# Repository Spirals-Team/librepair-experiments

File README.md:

# repairnator-experiments

This is an open-science repository with data related to ["How to Design a Program Repair Bot? Insights from the Repairnator Project"](https://hal.inria.fr/hal-01691496/document) (ICSE 2018) and [Repairnator patches programs automatically](https://ubiquity.acm.org/article.cfm?id=3349589), (Ubiquity, Association for Computing Machinery, 2019).

```Bibtex
@inproceedings{repairnator,
 title = {How to Design a Program Repair Bot? Insights from the Repairnator Project},
 author = {Urli, Simon and Yu, Zhongxing and Seinturier, Lionel and Monperrus, Martin},
 booktitle = {Proceedings of the 40th International Conference on Software Engineering},
 year = {2018}
}
```

This repository aims to contain the code of the failing Java projects and also information about the bugs reproduction, test failures and repair attempts using three different repair tools: [NPEFix](https://github.com/SpoonLabs/npefix), [Nopol](https://github.com/SpoonLabs/nopol), and [Astor](https://github.com/SpoonLabs/astor).

## Content of the repository

The structure of the repository is as follows:
* Branch `master` contains the `builds` folder and the documentation of this repository;
* The `builds` folder contains a specific JSON file obtained using the Travis CI API for every Travis CI build failure related to Java programs that use Maven as building tool;
* The `jobs` folder contains a subfolder for every build and each of them contains as many JSON files (obtained using the Travis CI API) as the number of jobs associated with that build;
* For each of these failing builds, there is a specific branch with all the information related to the building of the project, bug reproduction, failing tests and repair attempts.

More details about every entry listed above will be provided in the subsequent sections.

## Statistics

The repository contains the builds collected in the period February 2017 - September 2018.

There are currently 14.132 build JSON files in the `builds` folder, each of them associated with a Continuous Integration (CI) build failure of a Java program that uses Maven as building tool.

The name of these JSON files corresponds to the Travis CI build identifier and their content is the result of the Travis CI API V3 ```GET /build/{build.id}```. More details can be found on the [official documentation](https://docs.travis-ci.com/user/developer/#api-v3).

The `jobs` folder has a specific subfolder for every build (except for 25 builds in which the data are no more available through the Travis CI API) and the name of these subfolders corresponds with the build id to which they are associated. Every subfolder related to a build contains a distinct JSON file for every job associated with that build. The name of these JSON files corresponds to the Travis CI job identifier and their content is the result of the Travis CI API V3 ```GET /job/{job.id}```.

There are 14.132 different branches (excluding master branch), each of them associated with a build failure. In particular, every branch can have 2, 3 or 4 commits, as reported in the following table:

|                            | 2 commits   | 3 commits   | 4 commits   |
|----------------------------|:-----------:|:-----------:|:-----------:|
| **Number of the branches** | 15          | 13.870      | 247         |

Most of the branches have 3 commits, where:
* The first one is the failing one;
* The second one contains metadata and log infomation regarding the building of the project;
* The third one adds other information about the failure and the reproduction of the bug. In addition, it can contain a patch developed by an automatic program repair technique, if any.

The branches that have 2 commits have the same information of the branches with 3 commits, and the only difference is that it has been created a single commit with all the data that usually are separated in the second and the third commit.

The branches that have 4 commits have one commit (the third one) that contains also the human patch.

## Builds information extracted using Travis CI API

### States of the collected failing builds

A build can have different states, and as reported in the [official documentation of Travis CI](https://docs.travis-ci.com/user/for-beginners/#breaking-the-build), a build is considered broken when one or more of its jobs complete with a state that is not passed: `errored`, `failed`, or `canceled`.

In the following table, it is reported the number of collected builds based on their state:

|                            | failed      | passed      | errored     | canceled  |
|----------------------------|:-----------:|:-----------:|:-----------:|:---------:|
| **Number of builds**       | 13.178      | 895         | 47          | 12        |

### Trigger events of the collected failing builds

Every build is triggered by an event. In particular, in the following table we see the number of the collected builds that have been triggered by a specific event:

|                            | push        | pull request  | cron        | api      |
|----------------------------|:-----------:|:-------------:|:-----------:|:--------:|
| **Number of builds**       | 7.169       | 6.264         | 539         | 160      |

The event type `cron` means that the build has been triggered via the [Travis CI cron jobs](https://docs.travis-ci.com/user/cron-jobs/), that can run builds at regular scheduled intervals independently of whether any commits were pushed to the repository.

The event type `api` means that the build has been triggered using the Travis CI API.

### Duration of the collected failing builds

Using the information extracted from the Travis CI API, it is possible to know the duration of a build, where the term `duration` is intended as the wall clock time in seconds to produce and execute a build.

The following table shows the number of the builds per different intervals of duration:

|                                            | Number of the builds   |
|:------------------------------------------:|-----------------------:|
| **0 &lt; duration &le; 100**               |                 1.527  |
| **100 &lt; duration &le; 500**             |                 3.948  |
| **500 &lt; duration &le; 1.000**           |                 1.443  |
| **1.000 &lt; duration &le; 5.000**         |                 3.397  |
| **5.000 &lt; duration &le; 10.000**        |                 1.220  |
| **10.000 &lt; duration &le; 25.000**       |                 2.172  |
| **25.000 &lt; duration &le; 50.000**       |                   408  |
| **duration &gt; 50.000**                   |                    17  |

The minimum duration recorded has been 3 seconds (`build` [357685462](https://github.com/repairnator/repairnator-experiments/blob/master/builds/357685462.json), `branch` [as0kir-topjava-357685462-20180324-053259](https://github.com/repairnator/repairnator-experiments/tree/as0kir-topjava-357685462-20180324-053259)), while the maximum duration recorded has been 60.035 seconds (`build` [247511890](https://github.com/repairnator/repairnator-experiments/blob/master/builds/247511890.json), `branch` [apache-flink-247511890-20170627-234202_bugonly](https://github.com/repairnator/repairnator-experiments/tree/apache-flink-247511890-20170627-234202_bugonly)).

## Jobs information extracted using Travis CI API

### States of the jobs associated with a build

Using the Travis CI API, it is possibile to know also the state of the jobs associated with a specific build. In particular, a job can have four different states: `passed`, `errored`, `failed`, and `canceled`. As reported in the [official documentation of Travic CI](https://docs.travis-ci.com/user/for-beginners/#breaking-the-build), when one or more jobs have a state different from `passed`, the associated build is considered broken.

In the following table, it is reported the number of jobs associated with the collected builds based on their state:

|                            | passed      | errored     | failed      | canceled  |
|----------------------------|:-----------:|:-----------:|:-----------:|:---------:|
| **Number of jobs**         | 37.738      | 144         | 23.962      | 2.945     |

### Number of errored jobs per build

When a job is classified as `errored`, it means that a command in the `before_install`, `install`, or `before_script` phase returned a non-zero exit code. The job stops immediately.

In the following table it is possibile to see the number of errored jobs per build:

| Number of the errored jobs | Number of the builds |
|----------------------------|---------------------:|
| 0                          |               14.003 |
| 1                          |                   87 |
| 2                          |                    8 |
| 3                          |                    3 |
| 4                          |                    5 |
| 5                          |                    0 |
| 6                          |                    0 |
| > 6                        |                    1 |

The highest number of the errored jobs per build is 12 (`build` [332193968](https://github.com/repairnator/repairnator-experiments/blob/master/builds/332193968.json), `branch` [GJL-flink-332193968-20180123-111656_bugonly](https://github.com/repairnator/repairnator-experiments/tree/GJL-flink-332193968-20180123-111656_bugonly)). 

### Number of failed jobs per build

When a job is classified as `failed`, it means that a command in the `script` phase returned a non-zero exit code. The job continues to run until it completes.

In the following table it is possibile to see the number of failed jobs per build:

| Number of the failed jobs | Number of the builds |
|---------------------------|---------------------:|
| 0                         |                  926 |
| 1                         |                8.554 |
| 2                         |                2.514 |
| 3                         |                  901 |
| 4                         |                  512 |
| 5                         |                  187 |
| 6                         |                  193 |
| > 6                       |                  320 |

The highest number of the failed jobs per build is 58 (`build` [421480538](https://github.com/repairnator/repairnator-experiments/blob/master/builds/421480538.json) - `branch` [JWGmeligMeyling-blaze-persistence-421480538-20180828-125625](https://github.com/repairnator/repairnator-experiments/tree/JWGmeligMeyling-blaze-persistence-421480538-20180828-125625), and `build` [421505900](https://github.com/repairnator/repairnator-experiments/blob/master/builds/421505900.json) - `branch` [JWGmeligMeyling-blaze-persistence-421505900-20180828-141855](https://github.com/repairnator/repairnator-experiments/tree/JWGmeligMeyling-blaze-persistence-421505900-20180828-141855)).

### Number of canceled jobs per build

When a job is classified as `canceled`, it means that a user cancels the job before it completes.

In the following table it is possibile to see the number of canceled jobs per build:

| Number of the canceled jobs | Number of the builds |
|-----------------------------|---------------------:|
| 0                           |               13.834 |
| 1                           |                  159 |
| 2                           |                   15 |
| 3                           |                    4 |
| 4                           |                    4 |
| 5                           |                    0 |
| 6                           |                    2 |
| > 6                         |                   89 |

The highest number of the canceled jobs per build is 36. The are 41 builds with 36 canceled jobs (e.g., the `build` [335090924](https://github.com/repairnator/repairnator-experiments/blob/master/builds/335090924.json), `branch` [matsim-org-matsim-335090924-20180130-113656_bugonly](https://github.com/repairnator/repairnator-experiments/tree/matsim-org-matsim-335090924-20180130-113656_bugonly)).

## Builds information extracted using Repairnator

The data about bugs reproduction, test failures and repair attempts is stored in a specific branch for every build failure. In particular, every branch is linked to a build JSON file in `master` branch and, as well as containing the source code of the buggy program, it also has some files with the keyword `repairnator`in their name. 

### repairnator.json files

Every branch has a file called `repairnator.json` that contains the data reported in the following table:

| Parameter                | Description                                                                               |
|:-------------------------|:------------------------------------------------------------------------------------------|
| bugType                  | The type of the failing build.                                                             |
| bugCommit                | The URL of the bug commit in which it is possible to see the diff with the previous one.  |
| error-types              | The types of errors that occurred during the building of the project.                      |
| failingModule            | The failing Maven module.                                    |
| failing-test-cases       | The list of the failing test cases.                                                       |
| hostname                 | The hostname used to run the Repairnator inspector.                                          |
| metrics                  | It contains information about the program associated with the failing build, such as the number of program files, the number of test cases and the number of used libraries. It also contains other information, such as the duration expressed in seconds to reproduce the bug, the date of the buggy build, and the date of the bug reproduction.                                                                                                      |
| repo                     | The name of the repository associated with the failing build.                             |
| totalNumberErroringTests | The total number of the erroring test cases.                                              |
| totalNumberFailingTests  | The total number of the failing test cases.                                               |
| totalNumberRunningTests  | The total number of the running test cases.                                               |
| totalNumberSkippingTests | The total number of the skipping test cases.                                              |

### Repairnator Maven files

Repairnator also collects information about the different phases of the Maven build life cycle. In particual, there are four different files. It is possible to see the number of the branches that have these files in the following table:

| File                                      | Number of the branches |
|:------------------------------------------|-----------------------:|
| repairnator.maven.buildproject.log        |                 12.855 |
| repairnator.maven.testproject.log         |                 12.855 |
| repairnator.maven.computeclasspath.log    |                 12.799 |
| repairnator.maven.resolvedependency.log   |                  7.841 |

* **repairnator.maven.buildproject.log**: it contains log information about the building of a project, such as the operations related to the goals of Apache Maven Resources plugin;
* **repairnator.maven.testproject.log**: it contains information about the execution of the test suite, such as the name of the executed test cases, and the number of the failing, running or skipped tests;
* **repairnator.maven.computeclasspath.log**: it contains log information about the creation of the classpath file;
* **repairnator.maven.resolvedependency.log**: it contains log information about the download of the necessary dependecies in order to build the project.

### Repairnator Nopol files

Nopol is one of the three program repair tools used in order to try to generate a patch for the failing builds. Nopol has been used since February 2017. The file `repairnator.nopol.results` contains information about its execution, such as its configuration and the allocated time. In the following table it is possible to see the number of the branches that contain this file:

| File                                      | Number of the branches |
|:------------------------------------------|-----------------------:|
| repairnator.nopol.results                 |                  8.910 |

### Repairnator NPEFix files

NPEFix is the second program repair tool used during the experiment and it has been used since August 2017. In particular, it has been exploited only when a `NullPointerException` has been encountered during the execution of the test suite. In the following table, there are the different files associated with the execution of NPEFix and the number of branches that have these files:

| File                                      | Number of the branches |
|:------------------------------------------|-----------------------:|
| repairnator.maven.nperepair.log           |                    921 |
| repairnator.maven.npefix.log              |                    715 |
| repairnator.npefix.results                |                    289 |

* **repairnator.maven.nperepair.log**: it contains Maven log information about the building of a project executed by NPEFix;
* **repairnator.maven.npefix.log**: it contains Maven log information about the execution of the test cases performed by NPEFix;
* **repairnator.npefix.results**: it contains information about the execution of NPEFix, such as if it was successful or not.

### Repairnator Astor files

Astor is the third program repair tool used during the experiment and it has been used starting from September 2017. There are four different files related to the execution of Astor that can be found in the branches, as reported in the following table:

| File                                      | Number of the branches |
|:------------------------------------------|-----------------------:|
| repairnator.astor.log                     |                  6.215 |
| repairnator.astor.mutation.log            |                  4.834 |
| repairnator.astor.results.json            |                  1.083 |
| repairnator.astor.mutation.results.json   |                    945 |

* **repairnator.astor.log**: it contains log information about the execution of Astor, starting from the beginning (e.g., the creation of the [Spoon](http://spoon.gforge.inria.fr) model);
* **repairnator.astor.mutation.log**: it contains log information about the execution of Astor, such as the modification points found with [GZoltar](http://www.gzoltar.com), and the mutation operators applied to these modification points in order to create a possible patch;
* **repairnator.astor.results.json**: it contains the statistics about Astor execution, such as the number of the patches found and the total time used for its execution;
* **repairnator.astor.mutation.results.json**: it contains information about the program variants created by Astor, such as the number of the variants successfully compiled and the number of program variants with compilation errors.

### Repairnator Patch folders

As reported in the following table, there are some branches that also have a folder containing the patches generated by the automatic program repair tools:

| Folder                                    | Number of the branches |
|:------------------------------------------|-----------------------:|
| repairnator-patches                       |                    120 |
| repairnatorPatches                        |                     52 |

### Types of the collected failing builds

In the following table, we have the number of the builds based on their type:

|                            | only_fail   | failing_passing |     
|----------------------------|:-----------:|:---------------:|
| **Number of the builds**   |      13.387 |             745 |

The type `failing_passing` means that the build failed because at least one test case failed, and the next build was a passing build that did not contain changes in the test files.

### Most common test failure types

Considering the 14.132 collected builds, we analyzed the different failure types occurred. `AssertionError` is the most common failure type with 8.475 occurences observed. The following table shows the top 10 common failure types observed:

| Failure type                         | Occurrences |
|:-------------------------------------|------------:|
| java.lang.AssertionError             |       8.475 |
| java.lang.NullPointerException       |       2.096 |
| org.junit.ComparisonFailure          |       1.291 |
| java.lang.IllegalStateException      |       1.281 |
| java.lang.RuntimeException           |         737 |
| java.lang.Exception                  |         722 |
| java.lang.NoClassDefFoundError       |         442 |
| junit.framework.AssertionFailedError |         437 |
| java.lang.IllegalArgumentException   |         420 |
| java.io.IOException                  |         404 |
| **Other**                            |       2.413 |
| **Total**                            |      18.718 |

On the contrary, taking into account only the custom exceptions, the top 10 common failure types observed are the following ones:

| Failure Type                                               | Occurrences |
|:---------------------------------------------------------- |------------:|
| org.postgresql.util.PSQLException                          |         228 |
| redis.clients.jedis.exceptions.JedisConnectionException    |         173 |
| redis.clients.jedis.exceptions.JedisException              |         163 |
| com.facebook.presto.spi.PrestoException                    |         132 |
| org.springframework.beans.factory.BeanCreationException    |         112 |
| org.openqa.selenium.WebDriverException                     |         105 |
| com.spotify.docker.client.exceptions.DockerException       |          96 |
| spoon.SpoonException                                       |          96 |
| com.mongodb.MongoTimeoutException                          |          95 |
| org.springframework.dao.DataAccessResourceFailureException |          84 |
| **Other**                                                  |       2.594 |
| **Total**                                                  |       3.878 |

Note that in `repairnator.json` files, the are some cases in which the same exception could be reported in two different ways. In particular, considering the values in the array `FailureNames` of JSON object `metrics`, there can be some `repairnator.json` files in which the exception has been saved with the correct name and others in which the exception has been saved with a single `:` at the end of the name. For instance, you can find both `java.lang.NullPointerException` and `java.lang.NullPointerException:`.

The complete list of these exceptions saved both with the correct name and with the symbol `:` at the end of the name is as follows:

* java.lang.NullPointerException;
* java.lang.ExceptionInInitializerError;
* java.lang.AssertionError;
* java.lang.NumberFormatException;
* java.io.FileNotFoundException;
* com.rgross.exception.CountyNotFoundException;
* java.util.concurrent.TimeoutException;
* java.lang.StackOverflowError;
* java.lang.IllegalStateException;
* java.lang.UnsupportedOperationException;
* junit.framework.AssertionFailedError;
* org.opentest4j.AssertionFailedError;
* com.objectia.twostep.exception.APIException;
* java.lang.RuntimeException;
* java.io.EOFException.

### Number of failing test cases per build

During the build process there can be many failing test cases. In the following table it is possible to see the number of the builds based on the number of their failing test cases:

| Number of the failing test cases           | Number of the builds   |
|:------------------------------------------:|-----------------------:|
| **0**                                      |                 5.023  |
| **1**                                      |                 3.140  |
| **2**                                      |                 2.957  |
| **3**                                      |                   545  |
| **4**                                      |                   601  |
| **5**                                      |                   177  |
| **6**                                      |                   734  |
| **&gt; 6**                                 |                   955  |

The highest number of the failing test cases observed in a single build has been 804 (`build` [412170129](https://github.com/repairnator/repairnator-experiments/blob/master/builds/412170129.json), `branch` [SeleniumHQ-htmlunit-driver-412170129-20180804-232323](https://github.com/repairnator/repairnator-experiments/tree/SeleniumHQ-htmlunit-driver-412170129-20180804-232323)).

### Number of erroring test cases per build

The number of the builds based on the number of their erroring test cases is reported in the following table:

| Number of the erroring test cases          | Number of the builds   |
|:------------------------------------------:|-----------------------:|
| **0**                                      |                 7.082  |
| **1**                                      |                 2.209  |
| **2**                                      |                   733  |
| **3**                                      |                   531  |
| **4**                                      |                   297  |
| **5**                                      |                   233  |
| **6**                                      |                   273  |
| **&gt; 6**                                 |                 2.774  |

The highest number of the erroring test cases observed in a single build has been 14.783 (`build` [376595276
](https://github.com/repairnator/repairnator-experiments/blob/master/builds/376595276.json), `branch` [druid-io-druid-376595276-20180509-013859](https://github.com/repairnator/repairnator-experiments/tree/druid-io-druid-376595276-20180509-013859)).

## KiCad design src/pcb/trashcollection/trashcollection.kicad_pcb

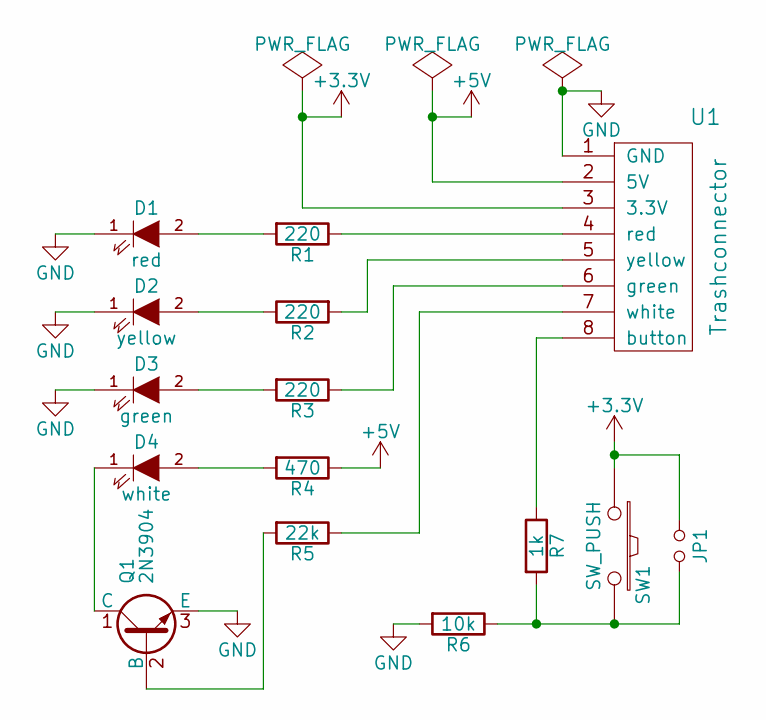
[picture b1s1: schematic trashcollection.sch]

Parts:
D1: red; LED_D3.0mm
D2: yellow; LED_D3.0mm
D3: green; LED_D3.0mm
D4: white; LED_D3.0mm
JP1: Jumper_NO_Small; Pin_Header_Straight_1x02_Pitch2.54mm
Q1: 2N3904; TO-92_Inline_Narrow_Oval
R1, R2, R3: 220; R_Axial_DIN0207_L6.3mm_D2.5mm_P10.16mm_Horizontal
R4: 470; R_Axial_DIN0207_L6.3mm_D2.5mm_P10.16mm_Horizontal
R5: 22k; R_Axial_DIN0207_L6.3mm_D2.5mm_P10.16mm_Horizontal
R6: 10k; R_Axial_DIN0207_L6.3mm_D2.5mm_P10.16mm_Horizontal
R7: 1k; R_Axial_DIN0207_L6.3mm_D2.5mm_P10.16mm_Horizontal
SW1: SW_PUSH; SW_PUSH-12mm
U1: Trashconnector; Pin_Header_Straight_1x08_Pitch2.54mm

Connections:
+3V3: JP1.1, SW1.1, U1.3 (3.3V)
+5V: R4.1, U1.2 (5V)
GND: D1.1 (K), D2.1 (K), D3.1 (K), Q1.3 (E), R6.2, U1.1 (GND)
unnamed: D1.2 (A), R1.2
unnamed: D2.2 (A), R2.1
unnamed: D3.2 (A), R3.2
unnamed: D4.1 (K), Q1.1 (C)
unnamed: D4.2 (A), R4.2
unnamed: JP1.2, R6.1, R7.2, SW1.2
unnamed: Q1.2 (B), R5.2
unnamed: R1.1, U1.4 (red)
unnamed: R2.2, U1.5 (yellow)
unnamed: R3.1, U1.6 (green)
unnamed: R5.1, U1.7 (white)
unnamed: R7.1, U1.8 (button)

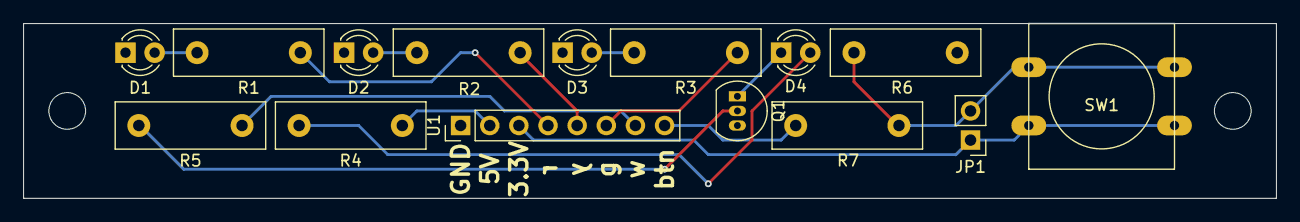
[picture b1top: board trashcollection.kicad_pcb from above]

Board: 2 copper layers, 109.2 x 15.2 mm, 15 parts (0 on the bottom side), 15 nets.

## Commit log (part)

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2018-08-29 End of the repairnator process
2018-08-29 Automatic repair information (optional automatic patches)
2018-08-29 Bug commit from the following repository mysql-time-machine/replicator This bug commit is a reflect of source code from: http://github.com/mysql-time-machine/replicator/commit/691c11dd1318542f0ae15e7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
2018-08-29 Bug commit from the following repository resteasy/Resteasy This bug commit is a reflect of source code from: http://github.com/resteasy/Resteasy/commit/f65a3ec8eff4eae992b546611323fdcbf6005791.
2018-08-29 Bug commit from the following repository vpro/vpro-shared This bug commit is a reflect of source code from: http://github.com/vpro/vpro-shared/commit/c1e95fe94b379f58c559196df7fcb06ce4bf89c0.
2018-08-29 Bug commit from the following repository Raaycc/inglesapp This bug commit is a reflect of source code from: http://github.com/Raaycc/inglesapp/commit/7fb8dc6f010cfdc0e10169b8929c7d15b79103ed.
2018-08-29 Bug commit from the following repository INRIA/spoon This bug commit is a reflect of source code from: http://github.com/INRIA/spoon/commit/857ae940875bcfe5e2fc47b03255f8dae534504d.
2018-08-29 Bug commit from the following repository IQSS/dataverse This bug commit is a reflect of source code from: http://github.com/IQSS/dataverse/commit/255f8372413f63193ae37f290c10c048e0758419.
2018-08-29 Bug commit from the following repository zentol/flink This bug commit is a reflect of source code from: http://github.com/zentol/flink/commit/a1a835bf2207b3a9a39eea006b6b648b0ed480b6.
2018-08-29 Bug commit from the following repository arcao/geocaching-api This bug commit is a reflect of source code from: http://github.com/arcao/geocaching-api/commit/ee58fed832fea4958a9b9b12a104d7d0e27deba0.
2018-08-29 Bug commit from the following repository houbb/charming This bug commit is a reflect of source code from: http://github.com/houbb/charming/commit/ee15a36cb74a37780eca74d843699b7c1c44ccc6.
2018-08-30 Bug commit from the following repository apache/incubator-druid This bug commit is a reflect of source code from: http://github.com/apache/incubator-druid/commit/3033e6ace27ff8dbe7164a600a1883cbd46f0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
2018-08-30 Bug commit from the following repository JMRI/JMRI This bug commit is a reflect of source code from: http://github.com/JMRI/JMRI/commit/0a03b0f25ca9be3b3f89191f6bef48ec461d080c.
2018-08-30 Bug commit from the following repository pabender/JMRI This bug commit is a reflect of source code from: http://github.com/pabender/JMRI/commit/759427b36be4401888fc619902336c09e061afef.
2018-08-30 Bug commit from the following repository apache/incubator-druid This bug commit is a reflect of source code from: http://github.com/apache/incubator-druid/commit/a0ba3a2fece9d02266f3acb0768b3efc012f9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
2018-08-30 Bug commit from the following repository apache/struts This bug commit is a reflect of source code from: http://github.com/apache/struts/commit/029892d656151eed00d3bbfbbb66f3480ef22572.
2018-08-30 Bug commit from the following repository salesforce/Argus This bug commit is a reflect of source code from: http://github.com/salesforce/Argus/commit/f31a1c66a5209e7a81715d65df11ec1f5f58a1c7.
2018-08-30 Bug commit from the following repository apache/incubator-servicecomb-saga This bug commit is a reflect of source code from: http://github.com/apache/incubator-servicecomb-saga/commit/74a4211b4fda18c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
2018-08-30 Bug commit from the following repository Lagarith/smart-logistic-tests This bug commit is a reflect of source code from: http://github.com/Lagarith/smart-logistic-tests/commit/25f5f006cb31f03fa093d2b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
2018-08-30 Bug commit from the following repository opentracing-contrib/java-cassandra-driver This bug commit is a reflect of source code from: http://github.com/opentracing-contrib/java-cassandra-driver/commit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
2018-08-30 Bug commit from the following repository algolia/algoliasearch-client-java-2 This bug commit is a reflect of source code from: http://github.com/algolia/algoliasearch-client-java-2/commit/31e51b452b1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
2018-08-30 Bug commit from the following repository 1and1/ejb-cdi-unit This bug commit is a reflect of source code from: http://github.com/1and1/ejb-cdi-unit/commit/15f5a555d5ea967e4d4865ea3e408c3261f35e34.
2018-08-30 Bug commit from the following repository opennars/opennars This bug commit is a reflect of source code from: http://github.com/opennars/opennars/commit/eeed4d13b03d3402e3a1a728c425db00d42772f8.
2018-08-30 Bug commit from the following repository lmaskisiki/khwela-messaging This bug commit is a reflect of source code from: http://github.com/lmaskisiki/khwela-messaging/commit/875da2fae3ab7fd64899895b2c5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
2018-08-30 Bug commit from the following repository diamondblack/incubator-dubbo This bug commit is a reflect of source code from: http://github.com/diamondblack/incubator-dubbo/commit/ff373a7db7645ea1b55bf8415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
2018-08-30 Bug commit from the following repository jmgreenberg/Hunter-ci-test This bug commit is a reflect of source code from: http://github.com/jmgreenberg/Hunter-ci-test/commit/449423d9046a85bd77836e40f7014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
2018-08-30 Bug commit from the following repository apache/incubator-servicecomb-saga This bug commit is a reflect of source code from: http://github.com/apache/incubator-servicecomb-saga/commit/0d851ddc845206f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
2018-08-30 Bug commit from the following repository zentol/flink This bug commit is a reflect of source code from: http://github.com/zentol/flink/commit/abe0d598e4dc8b51c836af53abd1f6bb2f3cc1be.
2018-08-30 Bug commit from the following repository salesforce/Argus This bug commit is a reflect of source code from: http://github.com/salesforce/Argus/commit/4fd8a312898083e9895bc7a5dc3ae0166e031785.
2018-08-30 Bug commit from the following repository scripnichenko/ryanair.com This bug commit is a reflect of source code from: http://github.com/scripnichenko/ryanair.com/commit/3a898a5943abd1d3533757ff1b89275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
2018-08-30 Bug commit from the following repository Azure/azure-libraries-for-java This bug commit is a reflect of source code from: http://github.com/Azure/azure-libraries-for-java/commit/87d2d8158aada585f8172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
2018-08-31 Bug commit from the following repository dannil/scb-java-client This bug commit is a reflect of source code from: http://github.com/dannil/scb-java-client/commit/21ff966cec48a06de93fab7dc2e58b81b5a6d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
2018-08-31 Bug commit from the following repository abraaoribeiro/ponto-inteligente This bug commit is a reflect of source code from: http://github.com/abraaoribeiro/ponto-inteligente/commit/213a5fa16d544dd3320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
2018-08-31 Bug commit from the following repository suniper/suniper-cenj This bug commit is a reflect of source code from: http://github.com/suniper/suniper-cenj/commit/556a11efbcd33cb909d1aef3576b6067ddcec54f.
2018-08-31 Bug commit from the following repository aspectran/aspectran This bug commit is a reflect of source code from: http://github.com/aspectran/aspectran/commit/73d6f94913dad3bd86f79ef9aca0827503e18c06.
2018-08-31 Bug commit from the following repository zerocracy/farm This bug commit is a reflect of source code from: http://github.com/zerocracy/farm/commit/6f118805dec52120882896cb64b94ebcf85b1203.
2018-08-31 Bug commit from the following repository Cognifide/aet This bug commit is a reflect of source code from: http://github.com/Cognifide/aet/commit/ce07e0be29a45fdeea745b383df75c69e09a9cff.
2018-08-31 Bug commit from the following repository podolsky4/TextMessenger This bug commit is a reflect of source code from: http://github.com/podolsky4/TextMessenger/commit/5810aa011ef7623c3b496c22fae9161bb8b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
2018-08-31 Bug commit from the following repository phax/peppol-smp-server This bug commit is a reflect of source code from: http://github.com/phax/peppol-smp-server/commit/c637060b061570ed31adfc271ffd974cec3df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
2018-08-31 Bug commit from the following repository Cantara/Whydah-UserIdentityBackend This bug commit is a reflect of source code from: http://github.com/Cantara/Whydah-UserIdentityBackend/commit/900286a8d6735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
2018-08-31 Bug commit from the following repository eclipse/hono This bug commit is a reflect of source code from: http://github.com/eclipse/hono/commit/d50759dc65120d54377a7925dd7599aaad3ae49a.
2018-08-31 Bug commit from the following repository sbunciak/testrex.io This bug commit is a reflect of source code from: http://github.com/sbunciak/testrex.io/commit/249aba4e04a5052da7832f28bb248025f827916c.
2018-08-31 Bug commit from the following repository rvesse/airline This bug commit is a reflect of source code from: http://github.com/rvesse/airline/commit/b542cd95ad41bef2f005489a5f4124bea8d4e0a3.
2018-08-31 Bug commit from the following repository rvesse/airline This bug commit is a reflect of source code from: http://github.com/rvesse/airline/commit/484f075bc91ecc78daf461a8df8edd189a1d7fd2.
2018-08-31 Bug commit from the following repository StanislavEsin/topjava This bug commit is a reflect of source code from: http://github.com/StanislavEsin/topjava/commit/6b7dd7d8a10d84b9e7fe670ecd513a27052fff2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
2018-08-31 Bug commit from the following repository bobjacobsen/JMRI This bug commit is a reflect of source code from: http://github.com/bobjacobsen/JMRI/commit/5514ec0828307f4245e07dd22e348215ce498045.
2018-08-31 Bug commit from the following repository SpoonLabs/astor This bug commit is a reflect of source code from: http://github.com/SpoonLabs/astor/commit/62c46e9e874e72295361417a6d9fdd4fe9f2c7a4.
2018-08-31 Bug commit from the following repository HubSpot/Singularity This bug commit is a reflect of source code from: http://github.com/HubSpot/Singularity/commit/0db0d420875ac84ea2417349a7ca6ecbc4f01a21.
2018-08-31 Bug commit from the following repository govind-menon/storm This bug commit is a reflect of source code from: http://github.com/govind-menon/storm/commit/8df4ce27c1c689bd1e0d1e771b2506f2e05dbefc.
2018-08-31 Bug commit from the following repository pagarme/pagarme-java This bug commit is a reflect of source code from: http://github.com/pagarme/pagarme-java/commit/191887a1dc9aeabd143cfc8a7d35fde1daa1ab64.
2018-09-01 Bug commit from the following repository kokosing/autobet This bug commit is a reflect of source code from: http://github.com/kokosing/autobet/commit/cde4fe5fba34be162fa38c6bfa9e176e534d6e60.
2018-09-01 Bug commit from the following repository Tickaroo/tikxml This bug commit is a reflect of source code from: http://github.com/Tickaroo/tikxml/commit/d8907351ed4b4a0e2d36a13c871a5a65160190e4.
2019-04-15 add builds JSON
2019-10-24 Removed the build JSON files with null value for the parameter 'started_at'
2019-10-30 Added information about the builds in the README
2019-10-30 Divided the repairnator files by type and added the information about the bug type
2019-10-30 Added information about the number of the builds with a certain number of failing/erroring test cases
2019-10-31 Updated the section "Builds Information extracted from the Travis CI API" of the README.md
2019-10-31 Added information about the Repairnator files in README.md
2019-10-31 Updated the information about the failing and erroring test cases in README.md
2019-10-31 Updated README.md
    Added the introduction for the section "Builds information extracted from the Travis CI API".
2019-11-01 Updated README.md
    Fixed the Bibtex element
2019-11-01 Updated README.md
    Added the note about the fact that there are some repairnator.json files in which the exception name has been saved both with the correct name and with a single ":" at the end of the name.
2019-11-02 Update README
    Updated the numbers in README.md after deleting build JSON files and corresponding branches associated with the builds collected in 2016, October 2018 and April 2019.
2019-11-11 Update README.md
    Added information about the jobs associated with the collected builds.
2019-11-11 Added jobs information associated with the collected builds
